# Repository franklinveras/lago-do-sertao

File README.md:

<h1>Projeto de Automação do Lago</h1>
Projeto simples de automação de um lago ornamental, com:
<ul>
    <li>Iluminação LED RGB submersa</li>
    <li>Duas bombas (uma para cascata e outra para filtros)</li>
    <li>Esterilizador UV</li>
    <li>Iluminação externa</li>
    <li>Controle das bombas</li>
    <li>Monitoramento de luminosidade</li>
    <li>Monitoramento de temperatura da água</li>
    <li>Navegação por menu utilizando um LCD 16x2, encoder e três botões.</li>
    <li>Controle por rádio nRF24l01+</li>
</ul>

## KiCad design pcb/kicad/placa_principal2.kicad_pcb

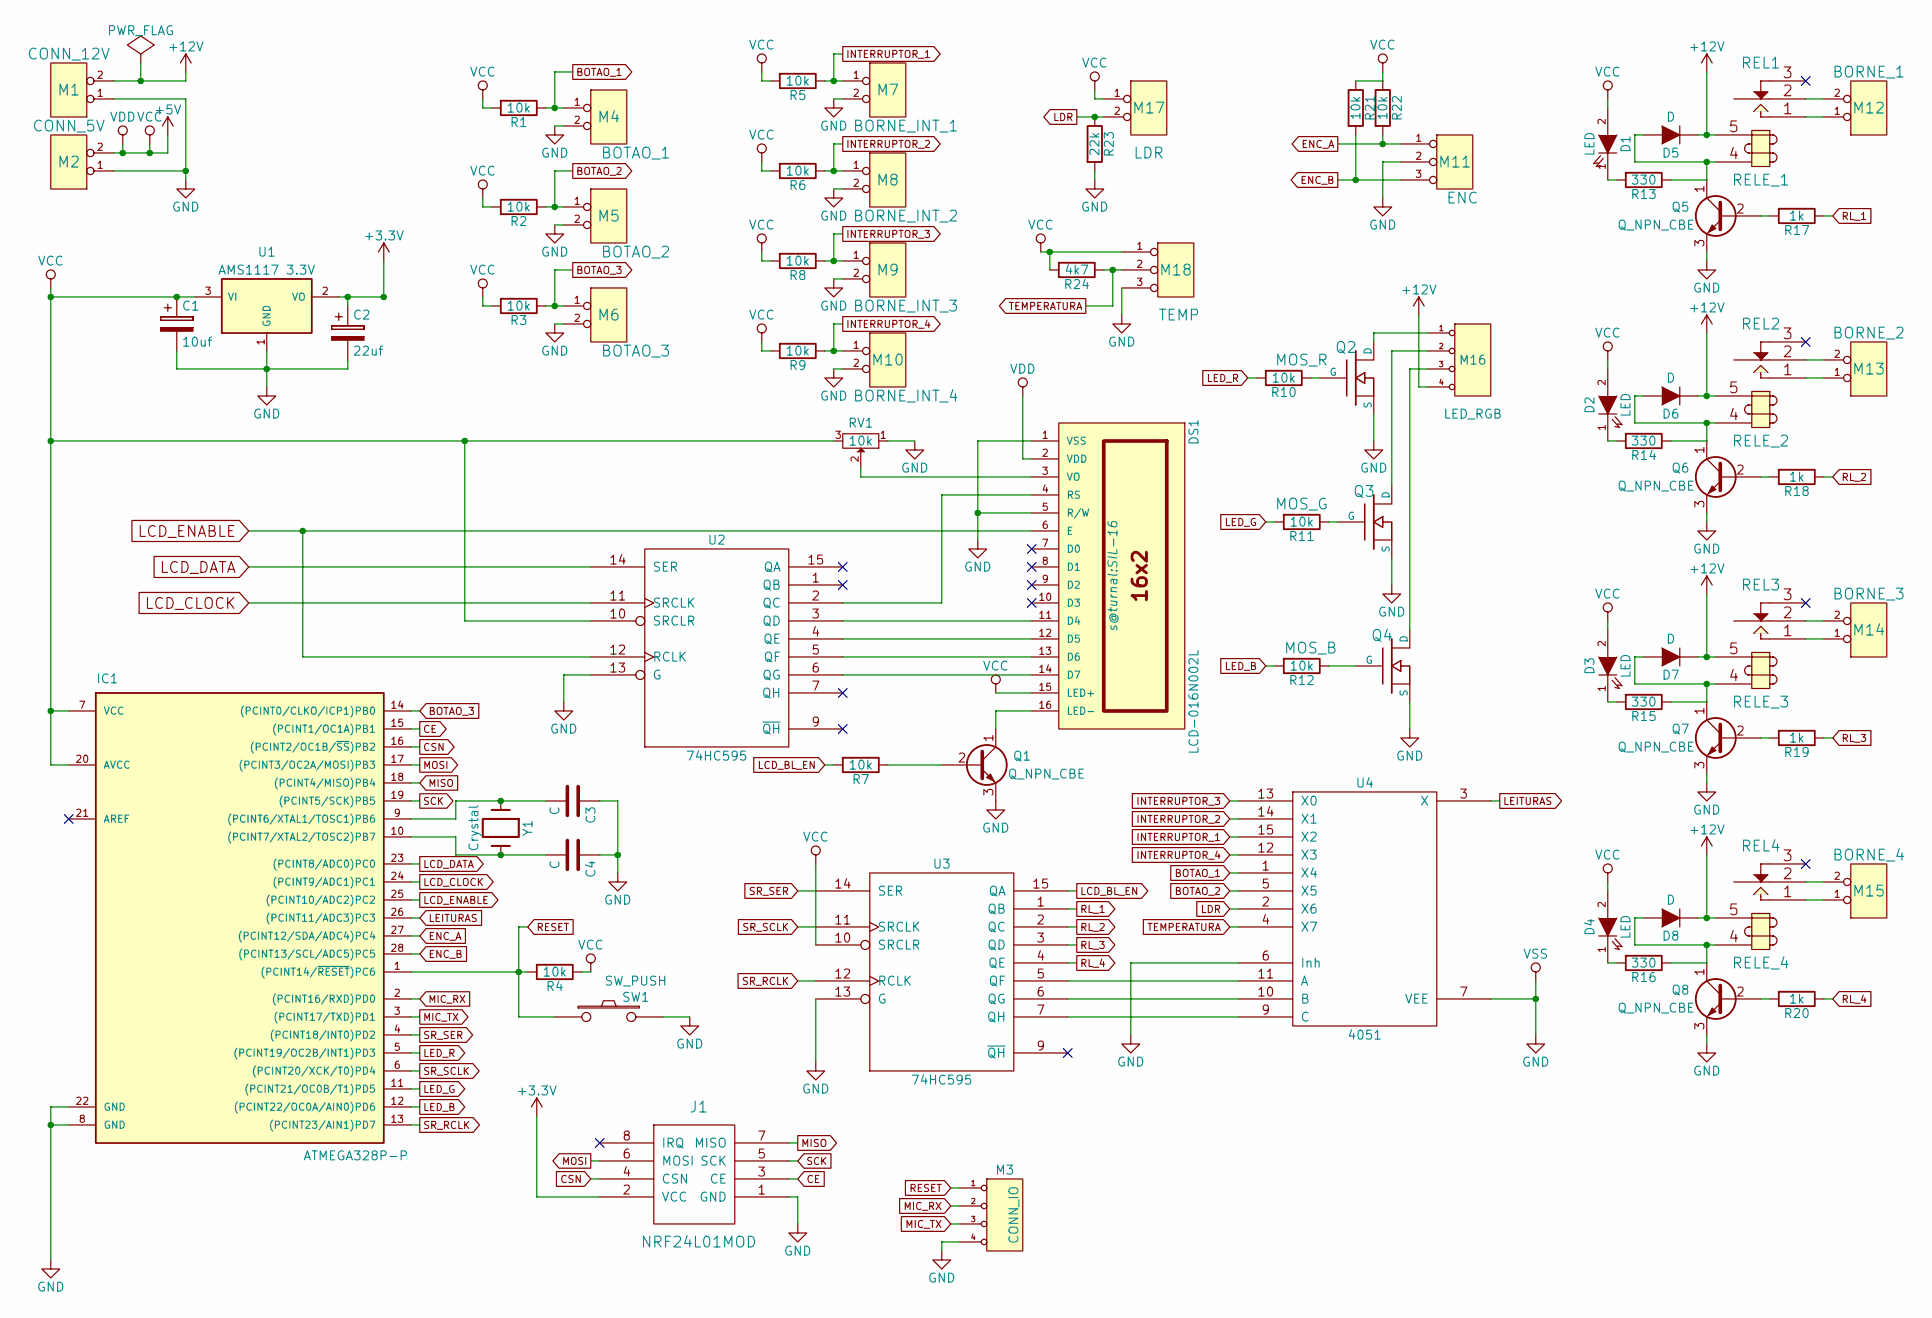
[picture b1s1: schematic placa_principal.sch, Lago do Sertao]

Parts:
C1: 10uf; C_Radial_D5_L11_P2
C2: 22uf; C_Radial_D5_L11_P2
C3, C4: C; C_Disc_D3_P2.5
D1, D2, D3, D4: LED; LED-3MM
D5, D6, D7, D8: D; Diode_DO-35_SOD27_Horizontal_RM10
DS1: LCD-016N002L; SIL-16
IC1: ATMEGA328P-P; DIP-28_W7.62mm_LongPads
J1: NRF24L01MOD; Pin_Header_Straight_2x04
M1: CONN_12V; SIL-2
M2: CONN_5V; SIL-2
M3: CONN_IO; SIL-4
M4: BOTAO_1; SIL-2
M5: BOTAO_2; SIL-2
M6: BOTAO_3; SIL-2
M7: BORNE_INT_1; bornier2
M8: BORNE_INT_2; bornier2
M9: BORNE_INT_3; bornier2
M10: BORNE_INT_4; bornier2
M11: ENC; SIL-3
M12: BORNE_1; bornier2
M13: BORNE_2; bornier2
M14: BORNE_3; bornier2
M15: BORNE_4; bornier2
M16: LED_RGB; bornier4
M17: LDR; bornier2
M18: TEMP; bornier3
Q1, Q5, Q6, Q7, Q8: Q_NPN_CBE; TO-92_Inline_Wide
Q2: MOS_R; TO220_GDS
Q3: MOS_G; TO220_GDS
Q4: MOS_B; TO220_GDS
R1, R2, R3, R4, R5, R6, R7, R8, R9, R10, R11, R12, R21, R22: 10k; Resistor_Horizontal_RM10mm
R13, R14, R15, R16: 330; Resistor_Horizontal_RM10mm
R17, R18, R19, R20: 1k; Resistor_Horizontal_RM10mm
R23: 22k; Resistor_Horizontal_RM10mm
R24: 4k7; Resistor_Horizontal_RM10mm
REL1: RELE_1; RELAY-1RG
REL2: RELE_2; RELAY-1RG
REL3: RELE_3; RELAY-1RG
REL4: RELE_4; RELAY-1RG
RV1: 10k; Potentiometer_Alps-RK163-single_15mm
SW1: SW_PUSH; SW_SPST_EVPBF
U1: AMS1117 3.3V; SOT-223
U2, U3: 74HC595; DIP-16_W7.62mm_LongPads
U4: 4051; DIP-16_W7.62mm_LongPads
Y1: Crystal; Crystal_HC49-U_Vertical

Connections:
+3V3: C2.1, J1.2 (VCC), U1.2 (VO)
+12V: D5.1 (K), D6.1 (K), D7.1 (K), D8.1 (K), M1.2, M16.4, REL1.5, REL2.5, REL3.5, REL4.5
BOTAO_1: M4.1, R1.1, U4.1 (X4)
BOTAO_2: M5.1, R2.1, U4.5 (X5)
BOTAO_3: IC1.14 ((PCINT0/CLKO/ICP1)PB0), M6.1, R3.1
CE: IC1.15 ((PCINT1/OC1A)PB1), J1.3 (CE)
CSN: IC1.16 ((PCINT2/OC1B/~SS~)PB2), J1.4 (CSN)
ENC_A: IC1.27 ((PCINT12/SDA/ADC4)PC4), M11.1, R22.2
ENC_B: IC1.28 ((PCINT13/SCL/ADC5)PC5), M11.3, R21.2
GND: C1.2, C2.2, C3.1, C4.1, DS1.1 (VSS), DS1.5 (R/W), IC1.8 (GND), IC1.22 (GND), J1.1 (GND), M1.1, M2.1, M3.4, M4.2, M5.2, M6.2, M7.2, M8.2, M9.2, M10.2, M11.2, M18.3, Q1.3 (E), Q2.S, Q3.S, Q4.S, Q5.3 (E), Q6.3 (E), Q7.3 (E), Q8.3 (E), R23.2, RV1.1, SW1.2, U1.1 (GND), U2.8 (GND), U2.13 (G), U3.8 (GND), U3.13 (G), U4.6 (Inh), U4.7 (VEE), U4.8 (VSS)
INTERRUPTOR_1: M7.1, R5.1, U4.15 (X2)
INTERRUPTOR_2: M8.1, R6.1, U4.14 (X1)
INTERRUPTOR_3: M9.1, R8.1, U4.13 (X0)
INTERRUPTOR_4: M10.1, R9.1, U4.12 (X3)
LCD_BL_EN: R7.2, U3.15 (QA)
LCD_CLOCK: IC1.24 ((PCINT9/ADC1)PC1), U2.11 (SRCLK)
LCD_DATA: IC1.23 ((PCINT8/ADC0)PC0), U2.14 (SER)
LCD_ENABLE: DS1.6 (E), IC1.25 ((PCINT10/ADC2)PC2), U2.12 (RCLK)
LDR: M17.2, R23.1, U4.2 (X6)
LED_B: IC1.12 ((PCINT22/OC0A/AIN0)PD6), R12.2
LED_G: IC1.11 ((PCINT21/OC0B/T1)PD5), R11.2
LED_R: IC1.5 ((PCINT19/OC2B/INT1)PD3), R10.2
LEITURAS: IC1.26 ((PCINT11/ADC3)PC3), U4.3 (X)
MIC_RX: IC1.2 ((PCINT16/RXD)PD0), M3.2
MIC_TX: IC1.3 ((PCINT17/TXD)PD1), M3.3
MISO: IC1.18 ((PCINT4/MISO)PB4), J1.7 (MISO)
MOSI: IC1.17 ((PCINT3/OC2A/MOSI)PB3), J1.6 (MOSI)
unnamed: C3.2, IC1.9 ((PCINT6/XTAL1/TOSC1)PB6), Y1.1
unnamed: C4.2, IC1.10 ((PCINT7/XTAL2/TOSC2)PB7), Y1.2
unnamed: D1.1 (K), R13.2
unnamed: D2.1 (K), R14.2
unnamed: D3.1 (K), R15.2
unnamed: D4.1 (K), R16.2
unnamed: D5.2 (A), Q5.1 (C), R13.1, REL1.4
unnamed: D6.2 (A), Q6.1 (C), R14.1, REL2.4
unnamed: D7.2 (A), Q7.1 (C), R15.1, REL3.4
unnamed: D8.2 (A), Q8.1 (C), R16.1, REL4.4
unnamed: DS1.3 (VO), RV1.2
unnamed: DS1.4 (RS), U2.2 (QC)
unnamed: DS1.11 (D4), U2.3 (QD)
unnamed: DS1.12 (D5), U2.4 (QE)
unnamed: DS1.13 (D6), U2.5 (QF)
unnamed: DS1.14 (D7), U2.6 (QG)
unnamed: DS1.16 (LED-), Q1.1 (C)
unnamed: M12.1, REL1.1 (T1)
unnamed: M12.2, REL1.2 (C1)
unnamed: M13.1, REL2.1 (T1)
unnamed: M13.2, REL2.2 (C1)
unnamed: M14.1, REL3.1 (T1)
unnamed: M14.2, REL3.2 (C1)
unnamed: M15.1, REL4.1 (T1)
unnamed: M15.2, REL4.2 (C1)
unnamed: M16.1, Q2.D
unnamed: M16.2, Q3.D
unnamed: M16.3, Q4.D
unnamed: Q1.2 (B), R7.1
unnamed: Q2.G, R10.1
unnamed: Q3.G, R11.1
unnamed: Q4.G, R12.1
unnamed: Q5.2 (B), R17.2
unnamed: Q6.2 (B), R18.2
unnamed: Q7.2 (B), R19.2
unnamed: Q8.2 (B), R20.2
unnamed: U3.5 (QF), U4.11 (A)
unnamed: U3.6 (QG), U4.10 (B)
unnamed: U3.7 (QH), U4.9 (C)
RESET: IC1.1 ((PCINT14/~RESET~)PC6), M3.1, R4.2, SW1.1
RL_1: R17.1, U3.1 (QB)
RL_2: R18.1, U3.2 (QC)
RL_3: R19.1, U3.3 (QD)
RL_4: R20.1, U3.4 (QE)
SCK: IC1.19 ((PCINT5/SCK)PB5), J1.5 (SCK)
SR_RCLK: IC1.13 ((PCINT23/AIN1)PD7), U3.12 (RCLK)
SR_SCLK: IC1.6 ((PCINT20/XCK/T0)PD4), U3.11 (SRCLK)
SR_SER: IC1.4 ((PCINT18/INT0)PD2), U3.14 (SER)
TEMPERATURA: M18.2, R24.1, U4.4 (X7)
VCC: C1.1, D1.2 (A), D2.2 (A), D3.2 (A), D4.2 (A), DS1.2 (VDD), DS1.15 (LED+), IC1.7 (VCC), IC1.20 (AVCC), M2.2, M17.1, M18.1, R1.2, R2.2, R3.2, R4.1, R5.2, R6.2, R8.2, R9.2, R21.1, R22.1, R24.2, RV1.3, U1.3 (VI), U2.10 (SRCLR), U2.16 (VCC), U3.10 (SRCLR), U3.16 (VCC), U4.16 (VDD)

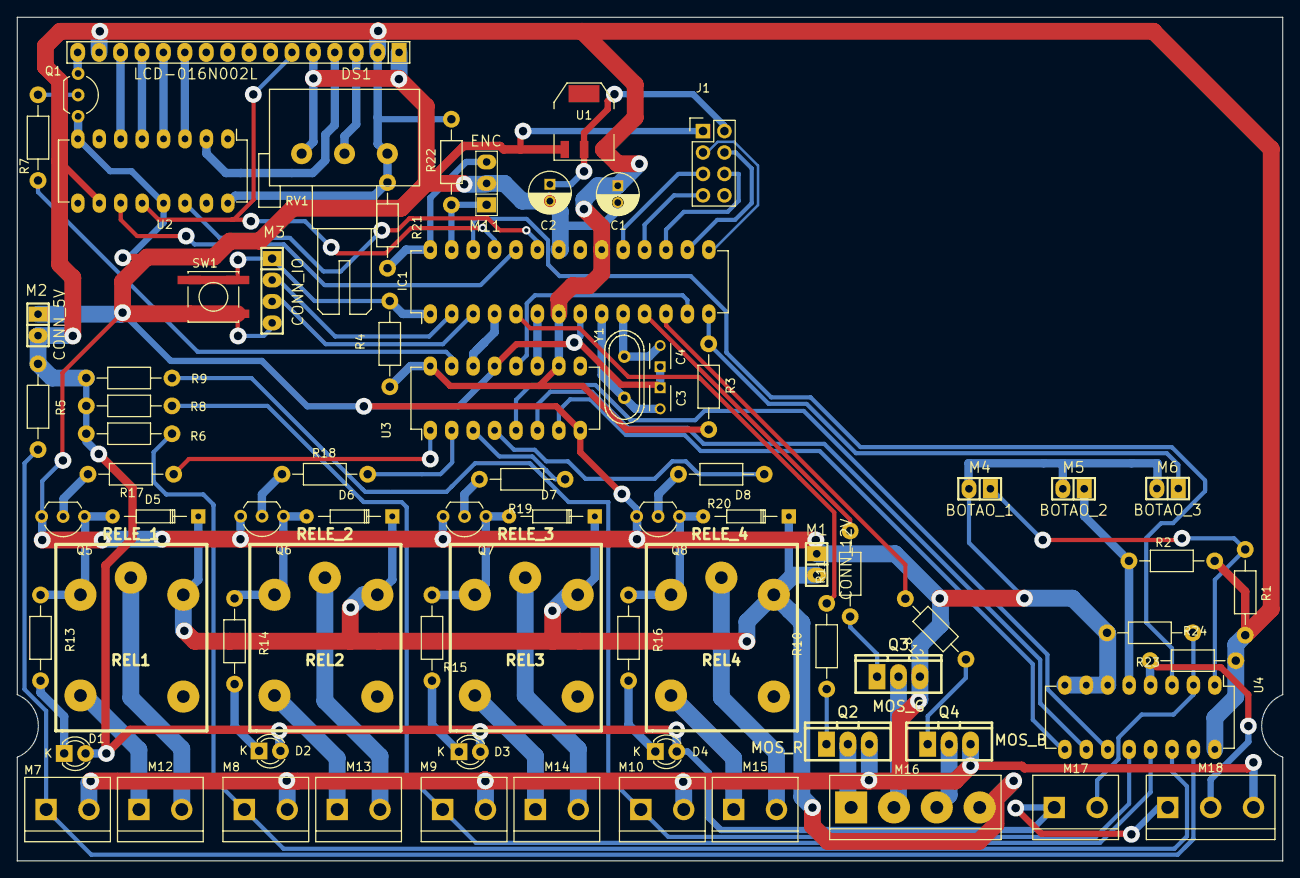
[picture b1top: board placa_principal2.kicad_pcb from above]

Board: 2 copper layers, 150.0 x 100.0 mm, 76 parts (0 on the bottom side), 77 nets.

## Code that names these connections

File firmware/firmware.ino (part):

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
/* ---------- Mapa de pinos do ATMEGA238P-PU ---------- */

const char LED_R_PIN = 3;
const char LED_G_PIN = 5;
const char LED_B_PIN = 6;

const char SR_DATA_PIN = 2;
const char SR_CLOCK_PIN = 4;
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const char RF_CE_PIN = 9;
const char RF_CSN_PIN = 10;

const char LCD_DATA_PIN = A0;
const char LCD_CLOCK_PIN = A1;
const char LCD_ENABLE_PIN = A2;

const char LEITURAS_PIN = A3;
const char ENC_A_PIN = A5;
const char ENC_B_PIN = A4;



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    ltc_state = (pino & 4);
    srWrite(lta_state, lta_state); /* Atualiza o 74HC595 para escolher o pino de leitura no 4051 */

    return analogRead(LEITURAS_PIN);
}

int srDigitalRead(char pino)
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
    srWrite(lta_state, lta_state);

    return digitalRead(LEITURAS_PIN);
}

/* ------------------- Mapa de pinos do 4051 ------------------- */
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char INT4_PIN = 3;
char BT1_PIN = 4;
char BT2_PIN = 5;
char LDR_PIN = 6;
char TEMP_PIN = 7;

boolean int4_def_state;
boolean int4_state;

/* ---------------  Ininicialização das classes ----------------- */
LiquidCrystal_SR lcd(LCD_DATA_PIN, LCD_CLOCK_PIN, LCD_ENABLE_PIN);
RotaryEncoder encoder(ENC_A_PIN, ENC_B_PIN);
RF24 radio(9,10);
/* ----------------- Informações do nRF24l01 -------------------- */
unsigned char radio_mensagem[2];
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
char led_modo = LED_MODO_DESLIGADO;
unsigned char led_brilho=255;
unsigned char led_r=0;
unsigned char led_g=0;
unsigned char led_b=0;
unsigned char led_velocidade=50;

unsigned char fade_seq[3][12]
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/* ----------------- Funções da fita LED RGB ---------------- */
void ledCor(unsigned char R, unsigned char G,unsigned char B)
{
    analogWrite(LED_R_PIN,R);
    analogWrite(LED_G_PIN,G);
    analogWrite(LED_B_PIN,B);
}

void ledMudaVelocidade(unsigned char velocidade)
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
    if (led_modo==LED_MODO_DESLIGADO)
    {
        digitalWrite(LED_R_PIN,LOW);
        digitalWrite(LED_G_PIN,LOW);
        digitalWrite(LED_B_PIN,LOW);
    }
    else
    {
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
    evento(EV_NULL);

    pinMode(LED_R_PIN, OUTPUT);
    pinMode(LED_G_PIN, OUTPUT);
    pinMode(LED_B_PIN, OUTPUT);
    pinMode(SR_DATA_PIN, OUTPUT);
    pinMode(SR_CLOCK_PIN, OUTPUT);
    pinMode(SR_LATCH_PIN, OUTPUT);
    pinMode(BT3_PIN, INPUT);
    pinMode(LEITURAS_PIN, INPUT);

    srWrite(lcd_bl_state, true);

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
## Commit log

2016-11-23 commit inicial
2016-11-24 Create README.md
    Criação do arquivo Leia-me
2016-11-24 Removidos desenhos de filtro em duplicata
2016-11-24 Removidos arquivos temporários de compilação
